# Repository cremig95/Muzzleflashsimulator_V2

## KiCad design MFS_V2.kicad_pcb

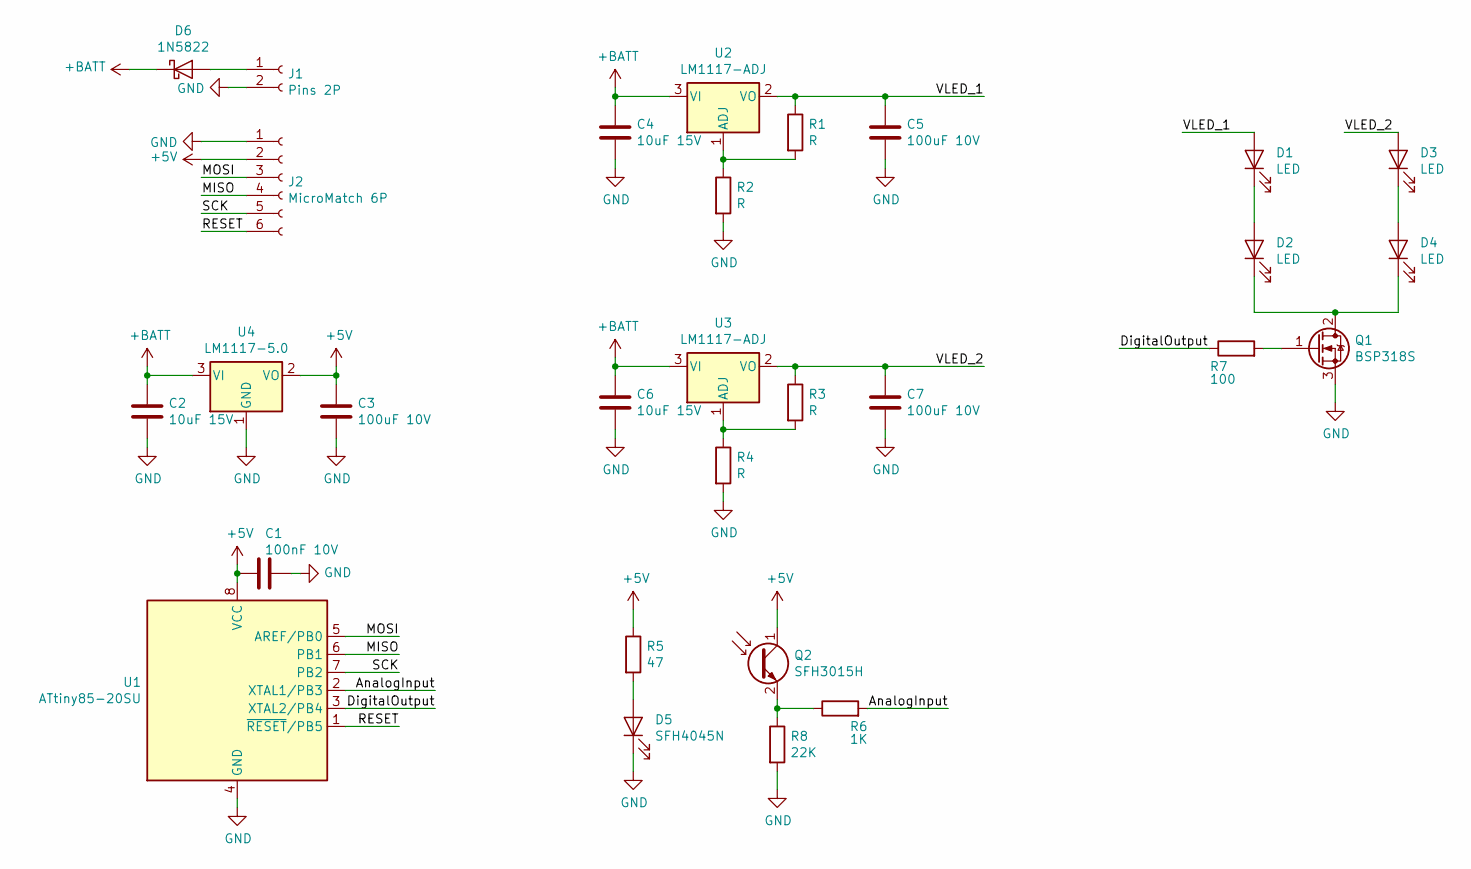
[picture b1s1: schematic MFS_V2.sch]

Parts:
C1: 100nF 10V; C_0603_1608Metric_Pad1.05x0.95mm_HandSolder
C2, C4, C6: 10uF 15V; C_0603_1608Metric_Pad1.05x0.95mm_HandSolder
C3, C5, C7: 100uF 10V; C_1210_3225Metric_Pad1.42x2.65mm_HandSolder
D1, D2, D3, D4: LED; LED_Cree-XQ_HandSoldering
D5: SFH4045N; LED_1210_3225Metric_Pad1.42x2.65mm_HandSolder
D6: 1N5822; D_SOD-123
J1: Pins 2P; PinHeader_1x02_P2.54mm_Vertical
J2: MicroMatch 6P; ConnectorMicromatch-6
Q1: BSP318S; SOT-223-3_TabPin2
Q2: SFH3015H; LED_1210_3225Metric_Pad1.42x2.65mm_HandSolder
R1, R2, R3, R4: R; R_0603_1608Metric_Pad1.05x0.95mm_HandSolder
R5: 47; R_0603_1608Metric_Pad1.05x0.95mm_HandSolder
R6: 1K; R_0603_1608Metric_Pad1.05x0.95mm_HandSolder
R7: 100; R_0603_1608Metric_Pad1.05x0.95mm_HandSolder
R8: 22K; R_0603_1608Metric_Pad1.05x0.95mm_HandSolder
U1: ATtiny85-20SU; SOIJ-8_5.3x5.3mm_P1.27mm
U2, U3: LM1117-ADJ; SOT-223-3_TabPin2
U4: LM1117-5.0; SOT-223-3_TabPin2

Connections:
+5V: C1.1, C3.1, J2.2, Q2.1 (C), R5.1, U1.8 (VCC), U4.2 (VO)
+BATT: C2.1, C4.1, C6.1, D6.1 (K), U2.3 (VI), U3.3 (VI), U4.3 (VI)
/AnalogInput: R6.2, U1.2 (XTAL1/PB3)
/DigitalOutput: R7.1, U1.3 (XTAL2/PB4)
/MISO: J2.4, U1.6 (PB1)
/MOSI: J2.3, U1.5 (AREF/PB0)
/RESET: J2.6, U1.1 (~RESET~/PB5)
/SCK: J2.5, U1.7 (PB2)
/VLED_1: C5.1, D1.2 (A), R1.1, U2.2 (VO)
/VLED_2: C7.1, D3.2 (A), R3.1, U3.2 (VO)
GND: C1.2, C2.2, C3.2, C4.2, C5.2, C6.2, C7.2, D5.1 (K), J1.2, J2.1, Q1.3 (S), R2.2, R4.2, R8.2, U1.4 (GND), U4.1 (GND)
unnamed: D1.1 (K), D2.2 (A)
unnamed: D2.1 (K), D4.1 (K), Q1.2 (D)
unnamed: D3.1 (K), D4.2 (A)
unnamed: D5.2 (A), R5.2
unnamed: D6.2 (A), J1.1
unnamed: Q1.1 (G), R7.2
unnamed: Q2.2 (E), R6.1, R8.1
unnamed: R1.2, R2.1, U2.1 (ADJ)
unnamed: R3.2, R4.1, U3.1 (ADJ)

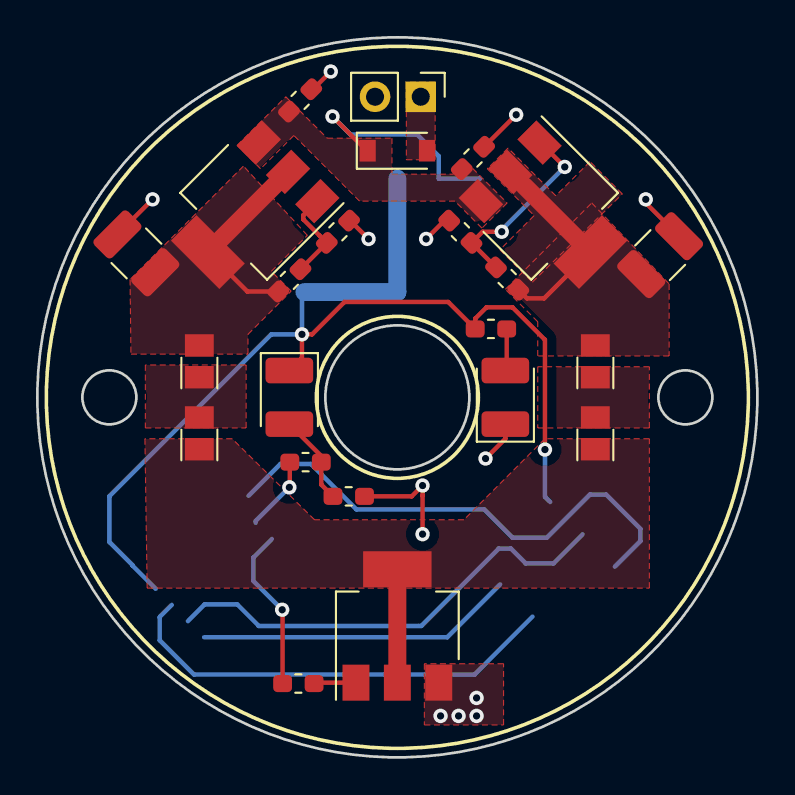
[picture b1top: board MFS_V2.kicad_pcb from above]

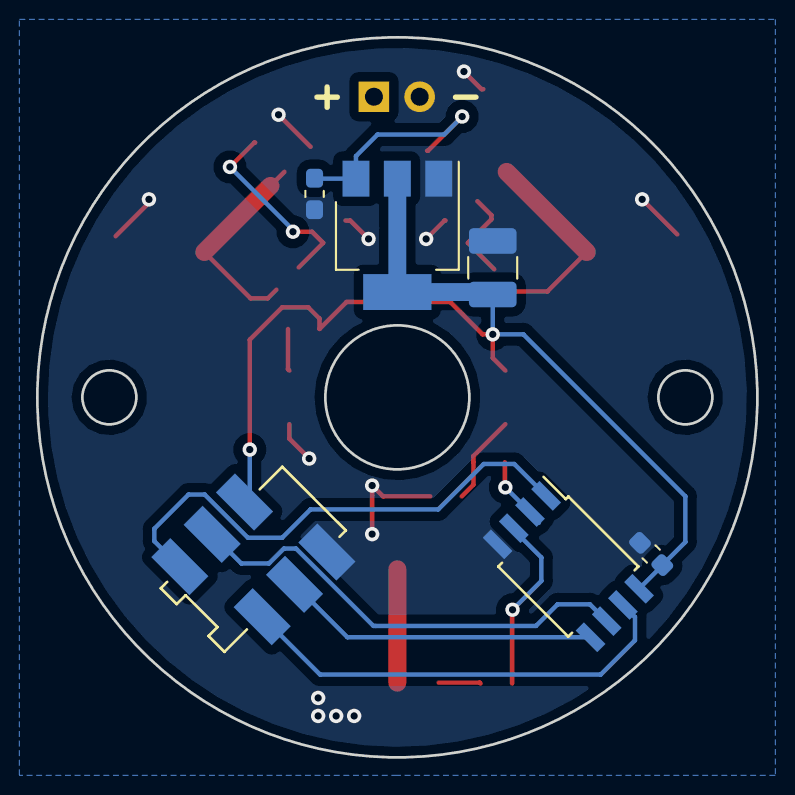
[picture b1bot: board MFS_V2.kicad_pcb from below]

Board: 2 copper layers, 40.0 x 40.0 mm, 29 parts (6 on the bottom side), 20 nets.

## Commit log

2019-05-17 First Upload
